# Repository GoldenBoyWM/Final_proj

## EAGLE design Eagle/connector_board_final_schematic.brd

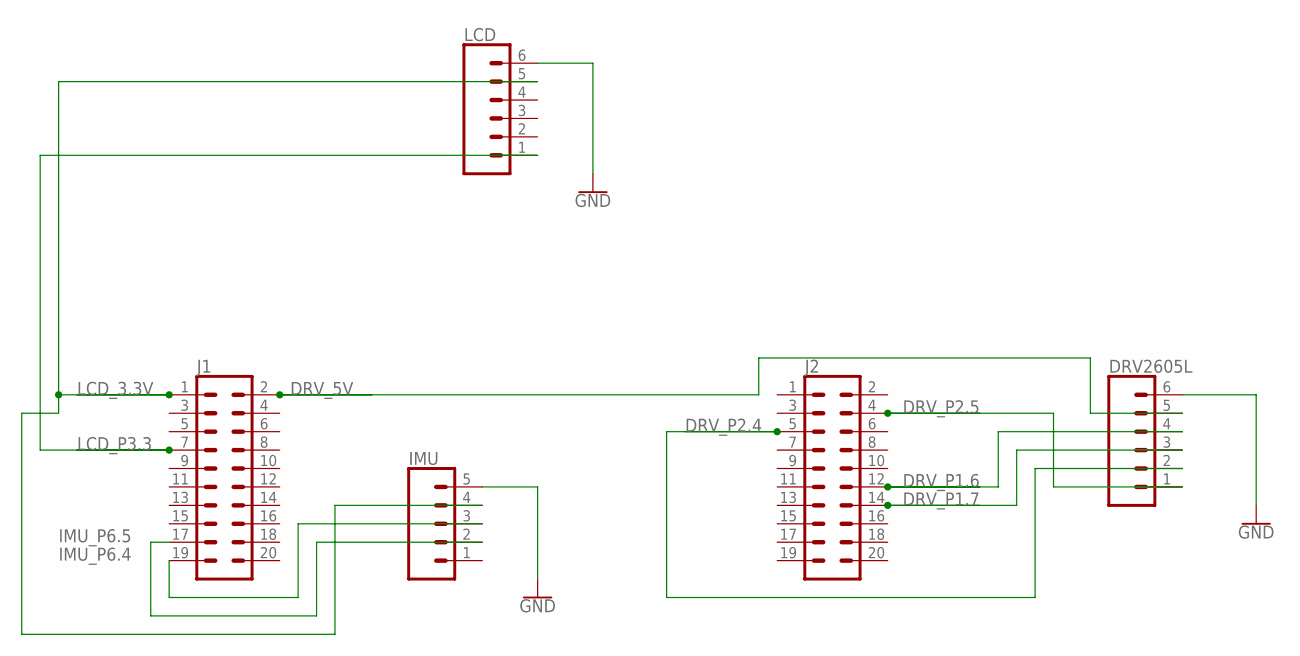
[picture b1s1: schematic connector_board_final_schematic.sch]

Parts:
DRV2605L: CONN_06SILK_FEMALE_PTH; 1X06
IMU: CONN_05; 1X05
J1, J2: CONN_10X2; 2X10
LCD: CONN_06SILK_FEMALE_PTH; 1X06

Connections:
DRV_5V: DRV2605L.5, J1.2
DRV_P1.6: DRV2605L.4, J2.12
DRV_P1.7: DRV2605L.3, J2.14
DRV_P2.4: DRV2605L.2, J2.5
DRV_P2.5: DRV2605L.1, J2.4
GND: DRV2605L.6, IMU.5, LCD.6
IMU_P6.4: IMU.3, J1.19
IMU_P6.5: IMU.2, J1.17
LCD_3.3V: IMU.4, J1.1, LCD.5
LCD_P3.3: J1.7, LCD.1

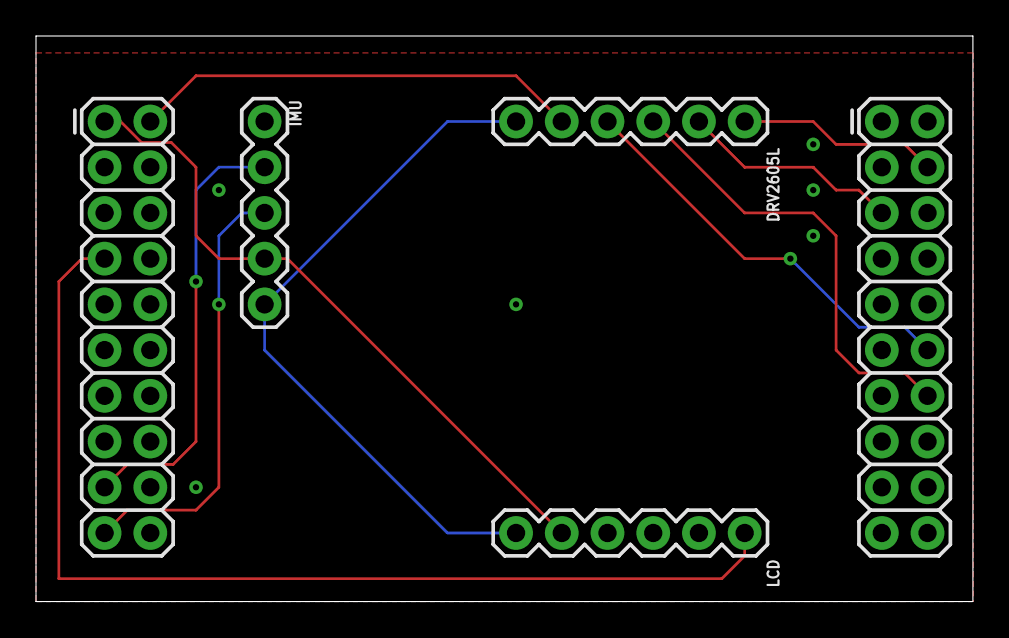
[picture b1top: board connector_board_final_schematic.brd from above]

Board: 2 copper layers, 52.0 x 31.4 mm, 5 parts (0 on the bottom side), 10 nets.

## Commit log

2019-12-17 should work
2019-12-17 Eagle schematic and PCB files
2019-12-17 manuals
2019-12-17 work?
2019-12-17 works?
2019-12-17 solidworks

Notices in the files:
parts and their libraries:
SparkFun-Connectors: Licensing: Creative Commons ShareAlike 4.0 International - https://creativecommons.org/licenses/by-sa/4.0
